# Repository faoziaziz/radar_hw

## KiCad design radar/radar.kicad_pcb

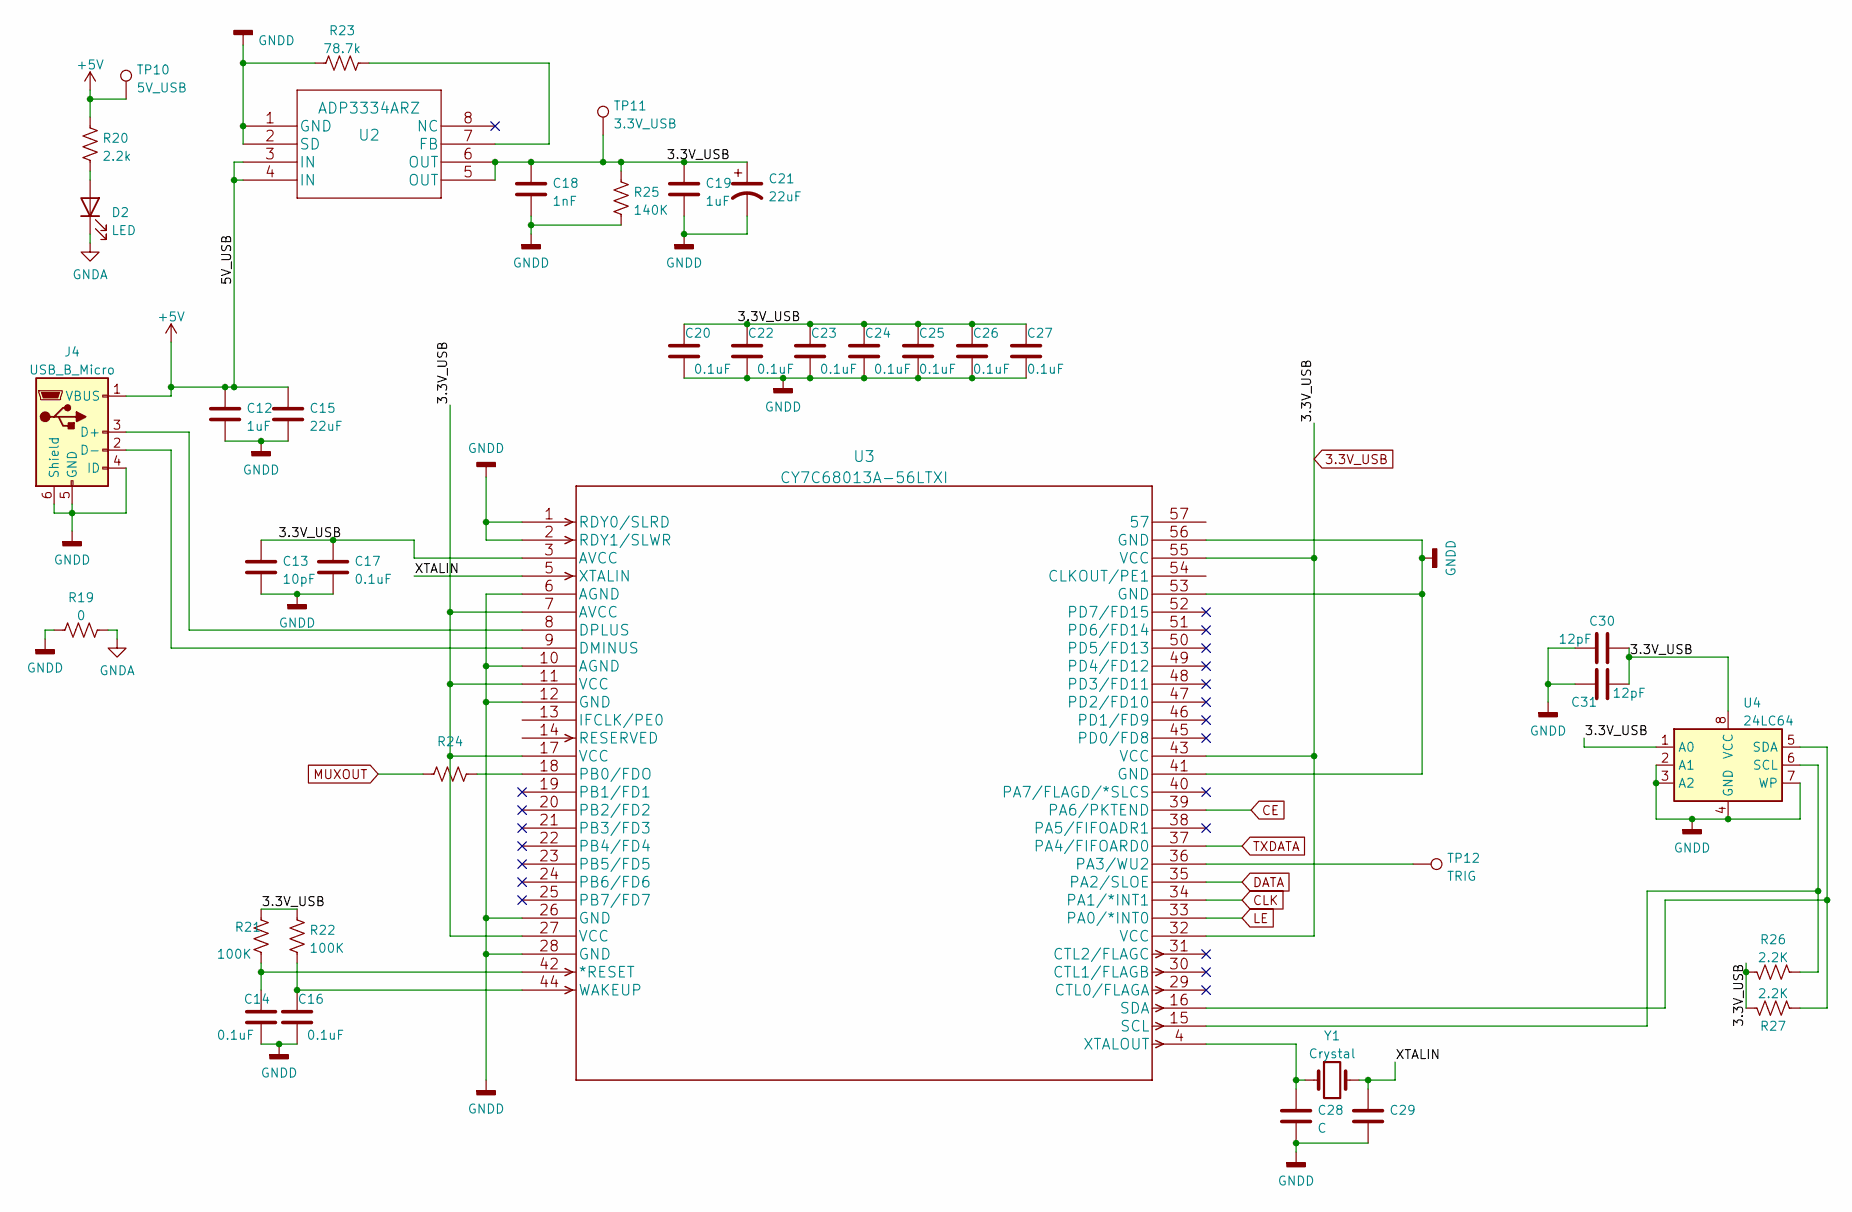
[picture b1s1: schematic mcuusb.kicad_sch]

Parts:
C12: 1uF; C_0603_1608Metric
C13: 10pF; C_0201_0603Metric_Pad0.64x0.40mm_HandSolder
C14, C16, C17, C20, C22, C23, C24, C25, C26, C27: 0.1uF; C_0201_0603Metric_Pad0.64x0.40mm_HandSolder
C15: 22uF; C_0603_1608Metric
C18: 1nF; R_0603_1608Metric
C19: 1uF; C_0402_1005Metric
C21: 22uF; C_0402_1005Metric
C28: C; C_0402_1005Metric
C29: C_0402_1005Metric
C30, C31: 12pF; C_0201_0603Metric_Pad0.64x0.40mm_HandSolder
D2: LED; LED_0201_0603Metric
J4: USB_B_Micro; USB_Micro-B_Molex-105133-0031
R19: 0; R_0201_0603Metric
R20: 2.2k; R_0201_0603Metric
R21, R22: 100K; R_0201_0603Metric
R23: 78.7k; R_0201_0603Metric_Pad0.64x0.40mm_HandSolder
R24: R_0201_0603Metric_Pad0.64x0.40mm_HandSolder
R25: 140K; R_0201_0603Metric
R26, R27: 2.2K; R_0201_0603Metric
TP10: 5V_USB; TestPoint_Loop_D1.80mm_Drill1.0mm_Beaded
TP11: 3.3V_USB; TestPoint_Loop_D1.80mm_Drill1.0mm_Beaded
TP12: TRIG; TestPoint_Pad_1.0x1.0mm
U2: ADP3334ARZ
U3: CY7C68013A-56LTXI
U4: 24LC64; TSSOP-8_3x3mm_P0.65mm
Y1: Crystal; Crystal_SMD_0603-2Pin_6.0x3.5mm

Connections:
3.3V_USB: C13.1, C17.1, C18.1, C19.1, C20.1, C21.1, C22.1, C23.1, C24.1, C25.1, C26.1, C27.1, C30.2, C31.2, R21.2, R22.2, R25.1, R26.1, R27.1, TP11.1, U2.5 (OUT), U2.6 (OUT), U3.3 (AVCC), U3.7 (AVCC), U3.11 (VCC), U3.17 (VCC), U3.27 (VCC), U3.32 (VCC), U3.43 (VCC), U3.55 (VCC), U4.1 (A0), U4.8 (VCC)
+5V: C12.1, C15.1, J4.1 (VBUS), R20.1, TP10.1, U2.3 (IN), U2.4 (IN); also elsewhere on the board
/MCU_USB/XTALIN: C29.1, U3.5 (XTALIN), Y1.2
CE: U3.39 (PA6/PKTEND); also elsewhere on the board
CLK: U3.34 (PA1/*INT1); also elsewhere on the board
DATA: U3.35 (PA2/SLOE); also elsewhere on the board
GNDA: D2.1 (K), R19.2; also elsewhere on the board
GNDD: C12.2, C13.2, C14.2, C15.2, C16.2, C17.2, C18.2, C19.2, C20.2, C21.2, C22.2, C23.2, C24.2, C25.2, C26.2, C27.2, C28.2, C29.2, C30.1, C31.1, J4.4 (ID), J4.5 (GND), J4.6 (Shield), R19.1, R23.1, R25.2, U2.1 (GND), U2.2 (SD), U3.1 (RDY0/SLRD), U3.2 (RDY1/SLWR), U3.6 (AGND), U3.10 (AGND), U3.12 (GND), U3.26 (GND), U3.28 (GND), U3.41 (GND), U3.53 (GND), U3.56 (GND), U4.2 (A1), U4.3 (A2), U4.4 (GND), U4.7 (WP)
LE: U3.33 (PA0/*INT0); also elsewhere on the board
MUXOUT: R24.1; also elsewhere on the board
unnamed: C14.1, R21.1, U3.42 (*RESET)
unnamed: C16.1, R22.1, U3.44 (WAKEUP)
unnamed: C28.1, U3.4 (XTALOUT), Y1.1
unnamed: D2.2 (A), R20.2
unnamed: J4.2 (D-), U3.9 (DMINUS)
unnamed: J4.3 (D+), U3.8 (DPLUS)
unnamed: R23.2, U2.7 (FB)
unnamed: R24.2, U3.18 (PB0/FDO)
unnamed: R26.2, U3.15 (SCL), U4.6 (SCL)
unnamed: R27.2, U3.16 (SDA), U4.5 (SDA)
unnamed: TP12.1, U3.36 (PA3/WU2)
TXDATA: U3.37 (PA4/FIFOARD0); also elsewhere on the board

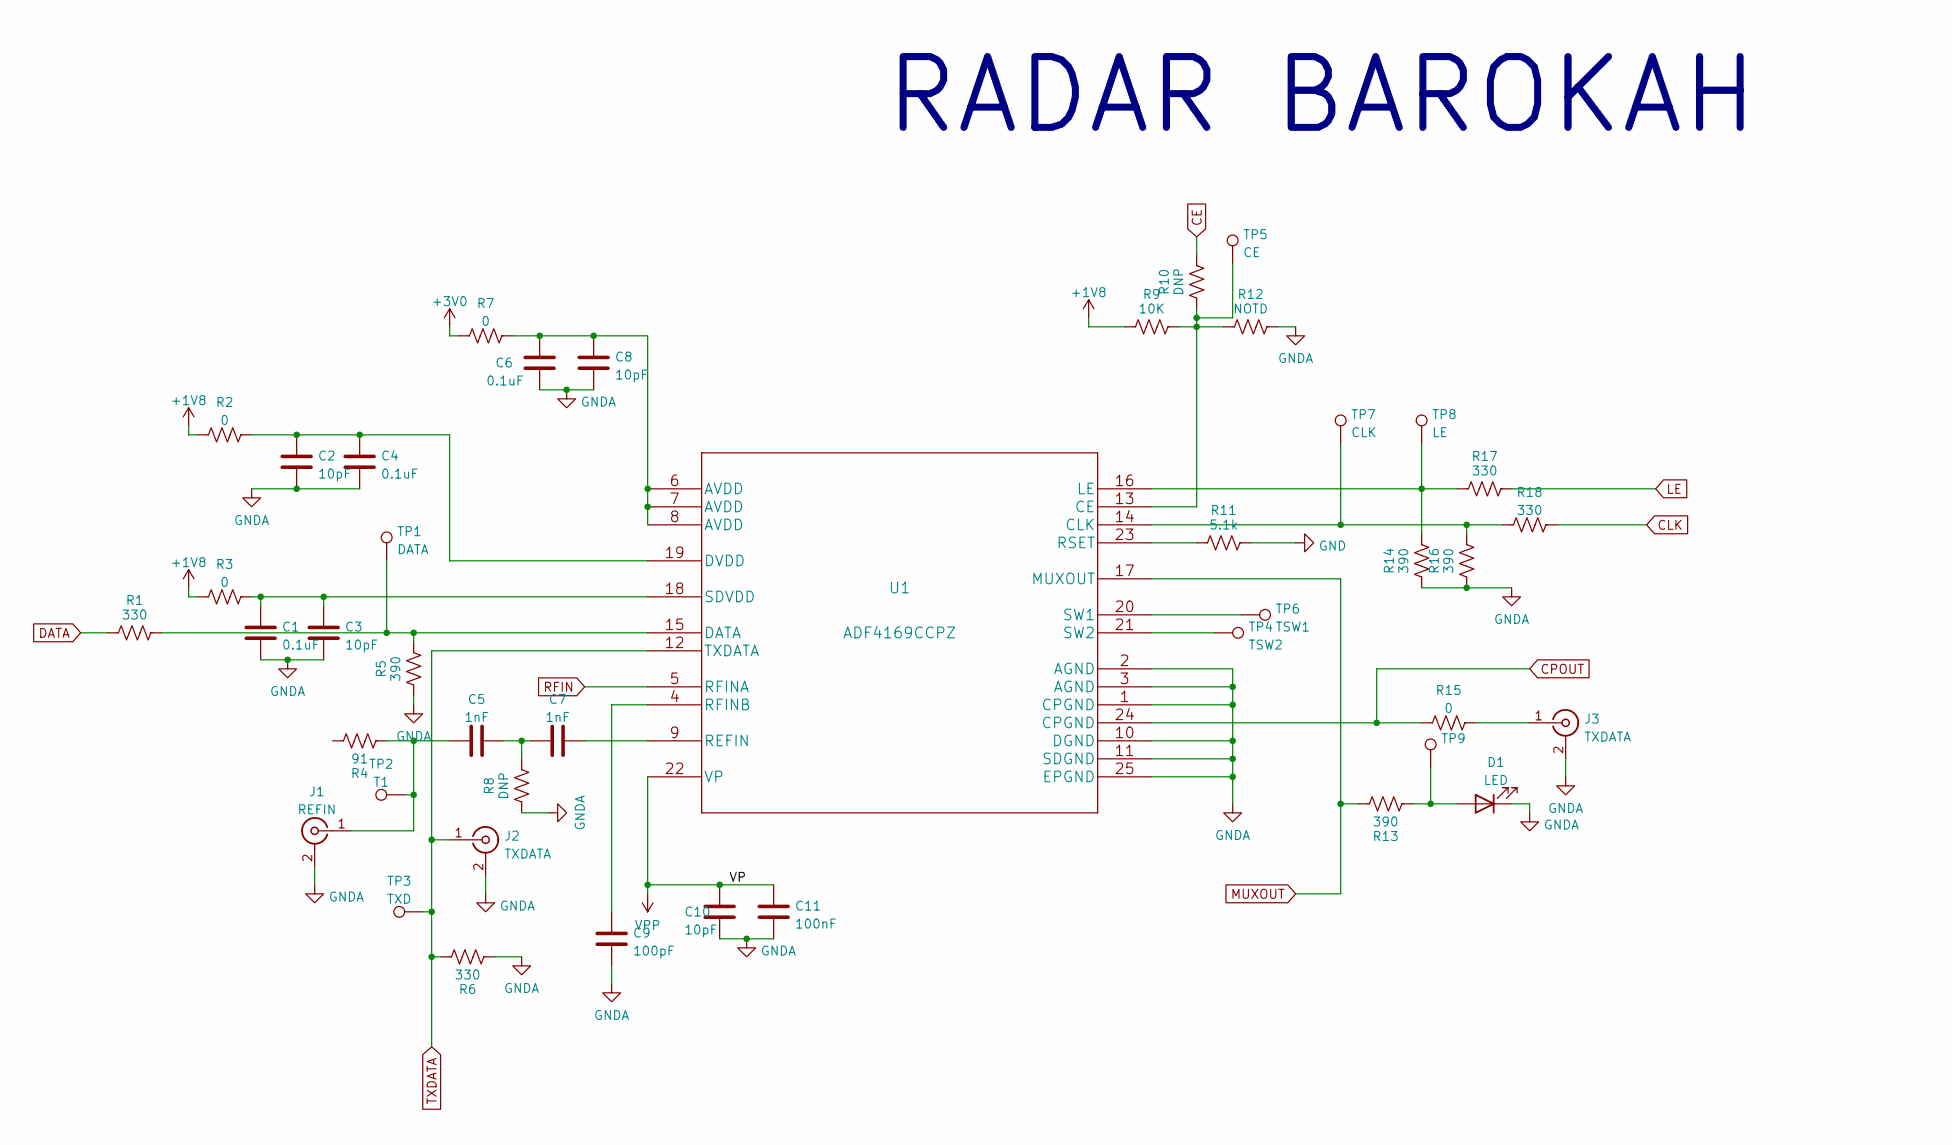
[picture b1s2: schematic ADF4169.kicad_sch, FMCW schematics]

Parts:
C1, C4, C6: 0.1uF; C_0201_0603Metric_Pad0.64x0.40mm_HandSolder
C2, C3, C8, C10: 10pF; C_0201_0603Metric_Pad0.64x0.40mm_HandSolder
C5, C7: 1nF; C_0201_0603Metric_Pad0.64x0.40mm_HandSolder
C9: 100pF; C_0201_0603Metric_Pad0.64x0.40mm_HandSolder
C11: 100nF; C_0201_0603Metric_Pad0.64x0.40mm_HandSolder
D1: LED; LED_0201_0603Metric_Pad0.64x0.40mm_HandSolder
J1: REFIN; U.FL_Molex_MCRF_73412-0110_Vertical
J2, J3: TXDATA; U.FL_Molex_MCRF_73412-0110_Vertical
R1, R6, R17, R18: 330; R_0201_0603Metric_Pad0.64x0.40mm_HandSolder
R2, R7: 0; R_0201_0603Metric
R3, R15: 0; R_0201_0603Metric_Pad0.64x0.40mm_HandSolder
R4: 91; R_0201_0603Metric_Pad0.64x0.40mm_HandSolder
R5, R13, R14, R16: 390; R_0201_0603Metric_Pad0.64x0.40mm_HandSolder
R8, R10: DNP; R_0201_0603Metric_Pad0.64x0.40mm_HandSolder
R9: 10K; R_0201_0603Metric_Pad0.64x0.40mm_HandSolder
R11: 5.1k; R_0201_0603Metric_Pad0.64x0.40mm_HandSolder
R12: NOTD; R_0201_0603Metric_Pad0.64x0.40mm_HandSolder
TP1: DATA; TestPoint_Loop_D1.80mm_Drill1.0mm_Beaded
TP2: T1; TestPoint_Loop_D1.80mm_Drill1.0mm_Beaded
TP3: TXD; TestPoint_Loop_D1.80mm_Drill1.0mm_Beaded
TP4: TSW2; TestPoint_Loop_D1.80mm_Drill1.0mm_Beaded
TP5: CE; TestPoint_Loop_D1.80mm_Drill1.0mm_Beaded
TP6: TSW1; TestPoint_Loop_D1.80mm_Drill1.0mm_Beaded
TP7: CLK; TestPoint_Loop_D1.80mm_Drill1.0mm_Beaded
TP8: LE; TestPoint_Loop_D1.80mm_Drill1.0mm_Beaded
TP9: TestPoint_Loop_D1.80mm_Drill1.0mm_Beaded
U1: ADF4169CCPZ

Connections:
+1V8: R2.2, R3.2, R9.1
+3V0: R7.1
CE: R10.2; also elsewhere on the board
CLK: R18.2; also elsewhere on the board
CPOUT: R15.1, U1.24 (CPGND); also elsewhere on the board
DATA: R1.1; also elsewhere on the board
GND: R11.2
GNDA: C1.2, C2.2, C3.2, C4.2, C6.2, C8.2, C9.2, C10.2, C11.1, D1.1 (K), J1.2 (Ext), J2.2 (Ext), J3.2 (Ext), R5.1, R6.1, R8.1, R12.2, R14.1, R16.1, U1.1 (CPGND), U1.2 (AGND), U1.3 (AGND), U1.10 (DGND), U1.11 (SDGND), U1.25 (EPGND); also elsewhere on the board
LE: R17.2; also elsewhere on the board
MUXOUT: R13.2, U1.17 (MUXOUT); also elsewhere on the board
unnamed: C1.1, C3.1, R3.1, U1.18 (SDVDD)
unnamed: C2.1, C4.1, R2.1, U1.19 (DVDD)
unnamed: C5.1, J1.1 (In), R4.1, TP2.1
unnamed: C5.2, C7.1, R8.2
unnamed: C6.1, C8.1, R7.2, U1.6 (AVDD), U1.7 (AVDD), U1.8 (AVDD)
unnamed: C7.2, U1.9 (REFIN)
unnamed: C9.1, U1.4 (RFINB)
unnamed: D1.2 (A), R13.1, TP9.1
unnamed: J3.1 (In), R15.2
unnamed: R1.2, R5.2, TP1.1, U1.15 (DATA)
unnamed: R9.2, R10.1, R12.1, TP5.1, U1.13 (CE)
unnamed: R11.1, U1.23 (RSET)
unnamed: R14.2, R17.1, TP8.1, U1.16 (LE)
unnamed: R16.2, R18.1, TP7.1, U1.14 (CLK)
unnamed: TP4.1, U1.21 (SW2)
unnamed: TP6.1, U1.20 (SW1)
RFIN: U1.5 (RFINA); also elsewhere on the board
TXDATA: J2.1 (In), R6.2, TP3.1, U1.12 (TXDATA); also elsewhere on the board
VPP: C10.1, C11.2, U1.22 (VP)

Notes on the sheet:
RADAR BAROKAH

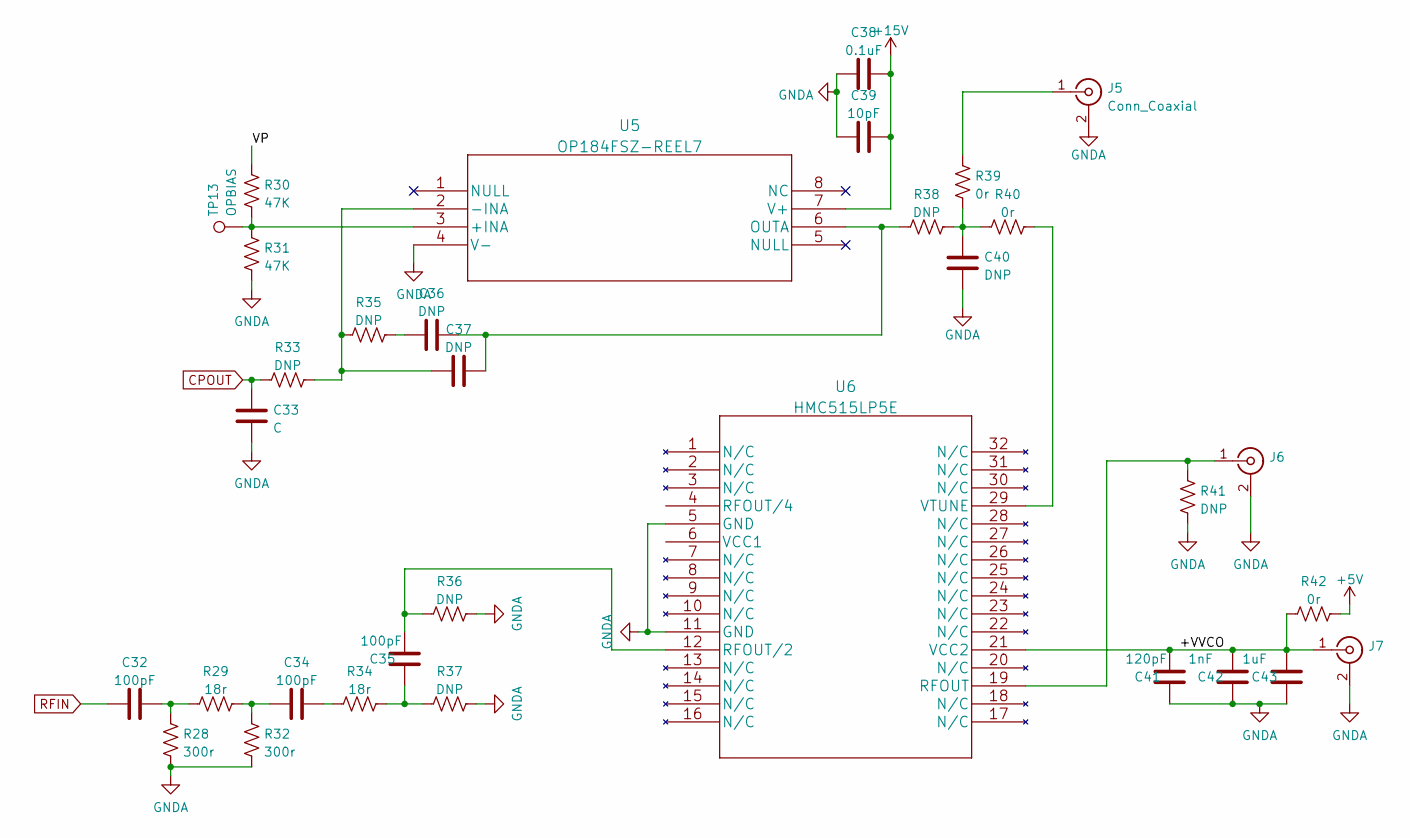
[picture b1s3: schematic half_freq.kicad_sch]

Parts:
C32, C34, C35: 100pF; C_0201_0603Metric_Pad0.64x0.40mm_HandSolder
C33: C; C_0402_1005Metric_Pad0.74x0.62mm_HandSolder
C36, C37: DNP; C_0402_1005Metric_Pad0.74x0.62mm_HandSolder
C38: 0.1uF; C_0201_0603Metric_Pad0.64x0.40mm_HandSolder
C39: 10pF; C_0201_0603Metric_Pad0.64x0.40mm_HandSolder
C40: DNP; C_0402_1005Metric
C41: 120pF; C_0201_0603Metric_Pad0.64x0.40mm_HandSolder
C42: 1nF; C_0201_0603Metric_Pad0.64x0.40mm_HandSolder
C43: 1uF; C_0201_0603Metric_Pad0.64x0.40mm_HandSolder
J5: Conn_Coaxial; U.FL_Molex_MCRF_73412-0110_Vertical
J6, J7: U.FL_Molex_MCRF_73412-0110_Vertical
R28, R32: 300r; R_0201_0603Metric_Pad0.64x0.40mm_HandSolder
R29, R34: 18r; R_0201_0603Metric_Pad0.64x0.40mm_HandSolder
R30, R31: 47K; R_0201_0603Metric_Pad0.64x0.40mm_HandSolder
R33, R35, R36, R37, R38, R41: DNP; R_0201_0603Metric_Pad0.64x0.40mm_HandSolder
R39, R40, R42: 0r; R_0201_0603Metric_Pad0.64x0.40mm_HandSolder
TP13: OPBIAS; TestPoint_Loop_D1.80mm_Drill1.0mm_Beaded
U5: OP184FSZ-REEL7
U6: HMC515LP5E

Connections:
+5V: R42.2; also elsewhere on the board
+15V: C38.2, C39.2, U5.7 (V+)
/half_freq/+VVCO: C41.2, C42.2, C43.2, J7.1 (In), R42.1, U6.21 (VCC2)
/half_freq/VP: R30.1
CPOUT: C33.1, R33.1; also elsewhere on the board
GNDA: C33.2, C38.1, C39.1, C40.1, C41.1, C42.1, C43.1, J5.2 (Ext), J6.2 (Ext), J7.2 (Ext), R28.2, R31.2, R32.2, R36.2, R37.2, R41.1, U5.4 (V-), U6.5 (GND), U6.11 (GND); also elsewhere on the board
unnamed: C32.2, R28.1, R29.1
unnamed: C34.1, R29.2, R32.1
unnamed: C34.2, R34.1
unnamed: C35.1, R34.2, R37.1
unnamed: C35.2, R36.1, U6.12 (RFOUT/2)
unnamed: C36.1, R35.2
unnamed: C36.2, C37.2, R38.1, U5.6 (OUTA)
unnamed: C37.1, R33.2, R35.1, U5.2 (-INA)
unnamed: C40.2, R38.2, R39.1, R40.1
unnamed: J5.1 (In), R39.2
unnamed: J6.1 (In), R41.2, U6.19 (RFOUT)
unnamed: R30.2, R31.1, TP13.1, U5.3 (+INA)
unnamed: R40.2, U6.29 (VTUNE)
RFIN: C32.1; also elsewhere on the board

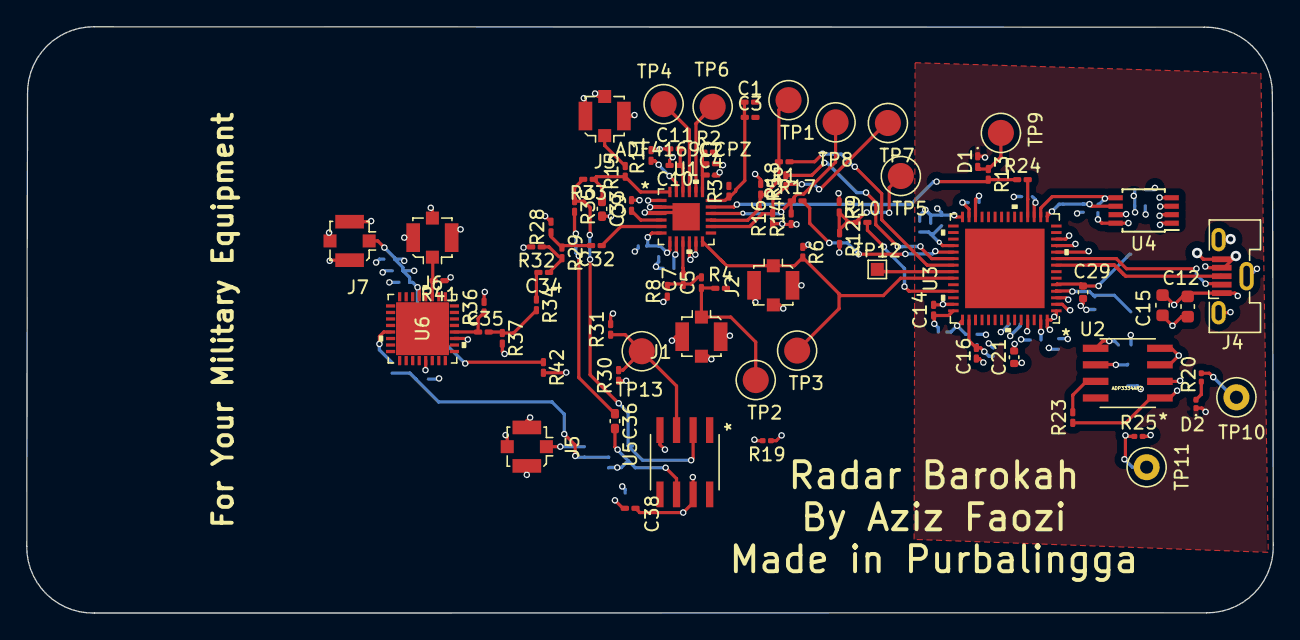
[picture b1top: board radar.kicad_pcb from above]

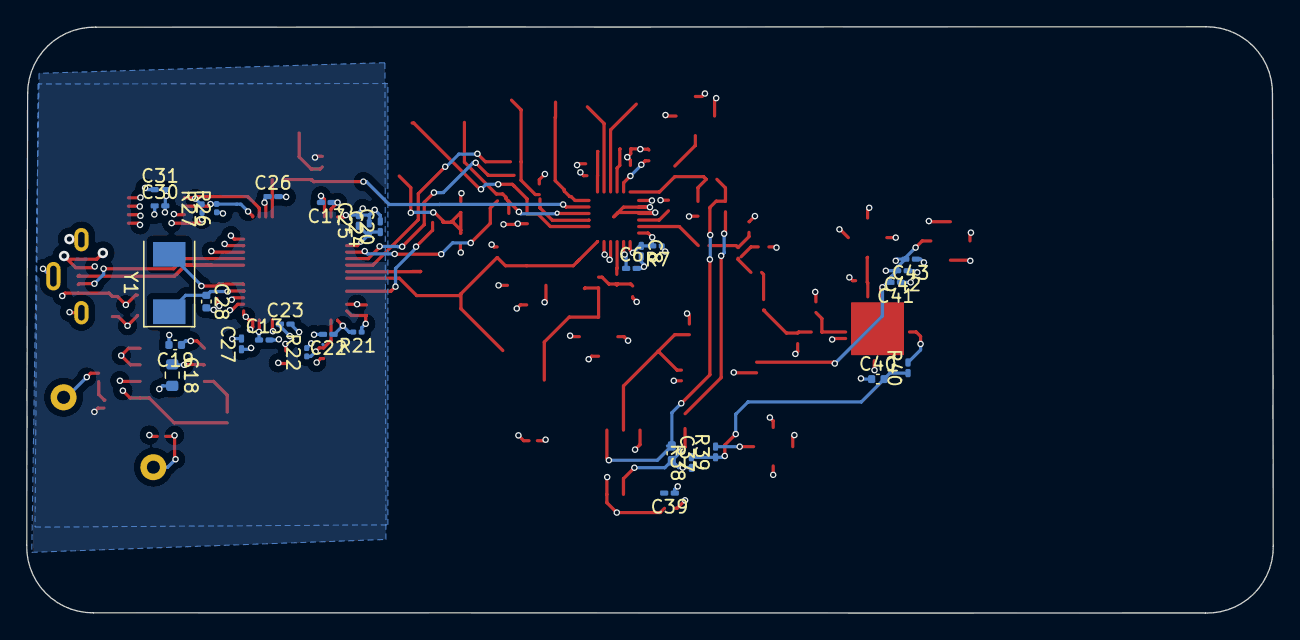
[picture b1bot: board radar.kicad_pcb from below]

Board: 4 copper layers, 95.6 x 45.0 mm, 114 parts (31 on the bottom side), 57 nets.

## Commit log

2022-04-26 add initial documents
2022-04-26 Set theme jekyll-theme-minimal
2022-04-26 add some revision
2022-04-26 mantap sekali

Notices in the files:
parts and their libraries:
Copyright 2021 Accelerated Designs. All rights reserved.
